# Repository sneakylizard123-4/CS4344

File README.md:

# CS4344 I2S DAC Breakout

**A compact 24-bit / 192 kHz stereo DAC for I2S audio projects.**

`SPDX-License-Identifier: CERN-OHL-P-2.0`

## Overview

The CS4344 is a 24-bit stereo DAC that accepts I2S audio and runs from a single 3.3 V supply. This board gives it a 6-pin 2.54 mm header, a 3.5 mm stereo jack, and the passives it needs. There is no configuration bus. The DAC is in hardware mode, so the host only has to provide clocks and data.

The PCB is 18.5 x 25.0 mm, two layers. The repository also includes a STEP assembly, a parametric 3D-printable case, and an ESP32-S3 test firmware example.

## Why I made this

I wanted a small, reusable I2S output board for FPGA and microcontroller projects.
The CS4344 is inexpensive, supports 24-bit / 192 kHz audio, and has a simple hardware interface.
The board has a real jack so it can be used outside a breadboard.

## Custom features

- 24-bit, up to 192 kHz stereo DAC.
- Hardware-mode I2S input. No I2C or SPI setup.
- Single 3.3 V supply.
- 6-pin 2.54 mm header for power and I2S.
- 3.5 mm stereo SMD jack.
- AC-coupled outputs with 3.3 uF series capacitors, 470 ohm series resistors, and 10 k bleed resistors.
- Compact 18.5 x 25.0 mm two-layer PCB.
- Two-part 3D-printable enclosure with a jack opening, header slot, and M2 screw posts.
- Full STEP assembly and parametric CadQuery source.

## How it works

The signal path is short: I2S comes in on J2, the CS4344 converts it, and the output network drives the jack.

| Block | Main parts | Function |
|---|---|---|
| I2S input | J2 | 3.3 V, ground, SD, SCK, FS, and MCLK |
| DAC | U1 | CS4344 stereo I2S DAC |
| Analog output | C6, C7, R1-R4, J1 | AC coupling, series resistance, and 3.5 mm output |
| Supply and reference decoupling | C1-C5 | VA, VQ, and FILT+ decoupling |

### Power tree

```text
J2.1  +3.3V ---+--- U1.9  VA
               |
               +--- C3 1 uF --- GND
               |
               +--- C5 100 nF --- GND

U1.5  VQ ------+--- C1 10 uF --- GND
               |
               +--- C2 100 nF --- GND

U1.6  FILT+ ---+--- C4 10 uF --- GND
```

The CS4344 is a 3.3 V part. Do not power the board from 5 V. VQ and FILT+ are internal reference/filter nodes; they are decoupled on the board and must not be driven from outside.

### I2S input

```text
J2.2  SD   -> U1.1  SDIN
J2.3  SCK  -> U1.2  SCLK
J2.4  FS   -> U1.3  LRCK
J2.5  MCLK -> U1.4  MCLK
```

The host must supply MCLK. There is no oscillator on the board. The CS4344 accepts several MCLK-to-FS ratios in hardware mode; check the datasheet for the ratio your host uses.

### Analog output

```text
U1.7  AOUTL -> C7 3.3 uF -> node L -> R4 470 ohm -> J1 tip
                              |
                              +-> R1 10 k -> GND

U1.10 AOUTR -> C6 3.3 uF -> node R -> R3 470 ohm -> J1 ring
                              |
                              +-> R2 10 k -> GND

J1 sleeve -> GND
```

Each output is AC-coupled so the DAC's DC bias does not appear at the jack. The 10 k resistor keeps the coupling capacitor's output node referenced to ground, and the 470 ohm resistor limits current into the cable. This is a line-level output, not a headphone amplifier. Use an external headphone amp or powered speakers if you need more drive.

## Schematic

The design is split into four KiCad sheets:

- [Root](images/schematic/01-root.png)
- [CS4344 and output network](images/schematic/02-cs4344.png)
- [3.5 mm jack](images/schematic/03-jack.png)
- [I2S header](images/schematic/04-connector.png)

## PCB design

- 18.5 x 25.0 mm board, 1.6 mm FR-4, two copper layers.
- 1 mm rounded corners.
- 0.2 mm signal traces, 0.5 mm output traces, 0.3 mm via drills.
- The board has no mounting holes.

| Top | Bottom |
|---|---|
|  |  |

More views:

- [Top 3D render](images/pcb/render-top.png)
- [Bottom 3D render](images/pcb/render-bottom.png)
- [Isometric 3D render](images/pcb/render-iso.png)

## Enclosure

The case is a two-part print: a base with screw posts and board ledges, and a lid with a header slot, registration lips, and a hold-down rib. The jack opening is on the right-hand wall. The lid is fixed with four M2 self-tapping screws. The outside size is 30 x 36 mm, 19.4 mm tall with the lid fitted and 20.8 mm including the screw heads.

| Assembled | Cutaway | Exploded |
|---|---|---|
|  |  |  |

The enclosure is parametric CadQuery. Edit the constants at the top of `cad/enclosure.py` and rerun the script to regenerate the STEP and STL files. The full board and case assembly is in `cad/CS4344-full-assembly.step`, and the board and electronics assembly is in `cad/CS4344-assembly.step`. It has not been printed or test-fitted yet.

Suggested print settings:

- 0.2 mm layer height
- 4 perimeters
- 20% infill
- PLA or PETG
- M2 x 8 mm self-tapping screws

## Usage

1. Connect 3.3 V to J2 pin 1 and ground to J2 pin 6.
2. Connect the host's I2S data, bit clock, and frame clock to SD, SCK, and FS.
3. Connect a master clock to MCLK. The board does not generate one.
4. Connect a 3.5 mm stereo cable from J1 to your amplifier or powered speakers.
5. Enable the I2S output on the host and start playback.

Use 3.3 V logic levels. The board does not include level shifters.

### Pinout

| J2 pin | Signal | Direction | Notes |
|---|---|---|---|
| 1 | +3.3V | Power in | 3.3 V only |
| 2 | SD | Input | I2S serial data |
| 3 | SCK | Input | I2S bit clock |
| 4 | FS | Input | I2S frame clock / LRCK |
| 5 | MCLK | Input | Master clock, required |
| 6 | GND | Power | Ground |

| J1 contact | Signal |
|---|---|
| Tip | Left channel |
| Ring | Right channel |
| Sleeve | Ground |

There is no firmware on the board. The host does all of the I2S setup. An ESP32-S3 test example is in `firmware/`.

## Firmware

The board has no MCU, so the firmware in `firmware/` runs on a host board. The example targets an ESP32-S3-DevKitC-1 and outputs a 1 kHz stereo sine at 48 kHz. It is meant as a bring-up test for the DAC and the analog output path.

`SPDX-License-Identifier: MIT`

| Signal | CS4344 J2 pin | ESP32-S3 pin |
|---|---|---|
| +3.3 V | 1 | 3V3 |
| SD | 2 | GPIO6 |
| SCK | 3 | GPIO4 |
| FS | 4 | GPIO5 |
| MCLK | 5 | GPIO7 |
| GND | 6 | GND |

The example runs I2S in standard mode with MCLK at 12.288 MHz, BCLK at 3.072 MHz, and LRCK at 48 kHz. It writes 24-bit samples left-aligned in 32-bit slots. The 32-bit slot keeps the 64 x Fs bit clock that the CS4344 expects. See [firmware/README.md](firmware/README.md) for the build, flash, and test steps.

```sh
cd firmware
pio run
pio run -t upload
pio device monitor
```

The example compiles but has not been run on a fabricated board yet.

## BOM

Prices are in USD and cover one set of electronics, the five-board JLCPCB minimum, and a 10-pack of M2 screws. Shipping, tax, and assembly fees are not included. The root [BOM.csv](BOM.csv) has a purchase link on every part line.

| Ref | Qty | Part | Package | Supplier | Part number | Unit price |
|---|---|---|---|---|---|---|
| U1 | 1 | CS4344-CZZR | TSSOP-10 | LCSC | C8952 | $1.5154 |
| J1 | 1 | SJ-3523-SMT-TR | SMD jack | Digi-Key | CP-3523SJCT-ND | $0.8800 |
| J2 | 1 | 1x6 2.54 mm female header | THT | LCSC | C40877 | $0.0889 |
| C1, C4 | 2 | 10 uF 10 V X5R | 0603 | LCSC | C19702 | $0.0272 |
| C2, C5 | 2 | 100 nF 50 V X7R | 0603 | LCSC | C14663 | $0.0084 |
| C3 | 1 | 1 uF 50 V X5R | 0603 | LCSC | C15849 | $0.0146 |
| C6, C7 | 2 | 3.3 uF 10 V X5R | 0603 | LCSC | C51412 | $0.0601 |
| R1, R2 | 2 | 10 k 1% | 0603 | LCSC | C25804 | $0.0022 |
| R3, R4 | 2 | 470 ohm 1% | 0603 | LCSC | C23179 | $0.0023 |
| PCB | 5 | CS4344 PCB | 18.5 x 25 mm | JLCPCB | - | $0.4000 |
| HW1 | 1 | M2 x 8 mm self-tapping screw, 10-pack | M2 | Motion RC | BCT5040-022 | $1.0900 |

| | |
|---|---:|
| Electronics subtotal | $2.6993 |
| 5 PCBs | $2.0000 |
| Screws, 10-pack | $1.0900 |
| **Total, excluding shipping and tax** | **$5.7893** |

That total buys one set of electronics, five bare PCBs, and a 10-pack of screws. You can build one board, keep four spare PCBs, and use 4 of the 10 screws.

The exact CUI jack is out of stock at LCSC. The Digi-Key part is the same SJ-3523-SMT-TR and was in stock when I checked.

## Production

Fabrication files are in `kicad/production/`:

- `CS4344.zip` - Gerbers and drill files.
- `bom.csv` - assembly BOM.
- `positions.csv` - pick-and-place positions.
- `designators.csv` - designator list.
- `netlist.ipc` - IPC netlist.

The board has not been ordered yet. The enclosure has not been printed yet.

## Repository structure

```text
CS4344/
|-- README.md
|-- JOURNAL.md
|-- BOM.csv
|-- LICENSE
|-- LICENSE-MIT
|-- .gitignore
|-- kicad/
|   |-- CS4344.kicad_pro
|   |-- CS4344.kicad_sch
|   |-- connector.kicad_sch
|   |-- cs4344.kicad_sch
|   |-- jack.kicad_sch
|   |-- CS4344.kicad_pcb
|   |-- sym-lib-table
|   |-- fabrication-toolkit-options.json
|   `-- production/
|       |-- CS4344.zip
|       |-- bom.csv
|       |-- designators.csv
|       |-- netlist.ipc
|       `-- positions.csv
|-- cad/
|   |-- enclosure.py
|   |-- CS4344-assembly.step
|   |-- CS4344-board.step
|   |-- CS4344-enclosure-base.step
|   |-- CS4344-enclosure-base.stl
|   |-- CS4344-enclosure-lid.step
|   |-- CS4344-enclosure-lid.stl
|   `-- CS4344-full-assembly.step
|-- firmware/
|   |-- README.md
|   |-- platformio.ini
|   `-- src/
|       `-- main.cpp
|-- images/
|   |-- schematic/       (screenshots as .png)
|   |-- pcb/             (editor screenshot)
|   |-- assembly/        (exploded)
|   `-- screenshots/     (timestamped progress images)
`-- blender/
    |-- CS4344.blend
    `-- CS4344.pcb3d
```

## Known issues

- The board has not been fabricated or tested. This is a first revision.
- The enclosure has not been printed or test-fitted.
- The lid counterbores are 4.2 mm across. Check the head diameter of the screws you buy and enlarge the counterbores if needed.
- The screws in the STEP assembly are simplified cylinders, not the exact screw geometry.
- The board has no mounting holes. It is held by the case ledges and lid rib.
- The CS4344 is TSSOP-10 with 0.5 mm pin pitch. It is not a good first hand-soldering project; use a stencil and hot air or reflow.
- The output is line level. It will not drive headphones directly.
- The ESP32-S3 firmware example compiles but has not been run on a fabricated board.

## Credits and inspiration

- Cirrus Logic for the CS4344 datasheet and reference circuit.
- KiCad for the schematic and PCB tools.
- CadQuery for the parametric enclosure.
- Hack Club Forge for the deadline and the push to document the project.

## License

Hardware design files and documentation are licensed under the CERN Open Hardware Licence Version 2 - Permissive (CERN-OHL-P-2.0). See [LICENSE](LICENSE).

`SPDX-License-Identifier: CERN-OHL-P-2.0`

The example firmware in `firmware/` is licensed under the MIT License. See [LICENSE-MIT](LICENSE-MIT).

`SPDX-License-Identifier: MIT`

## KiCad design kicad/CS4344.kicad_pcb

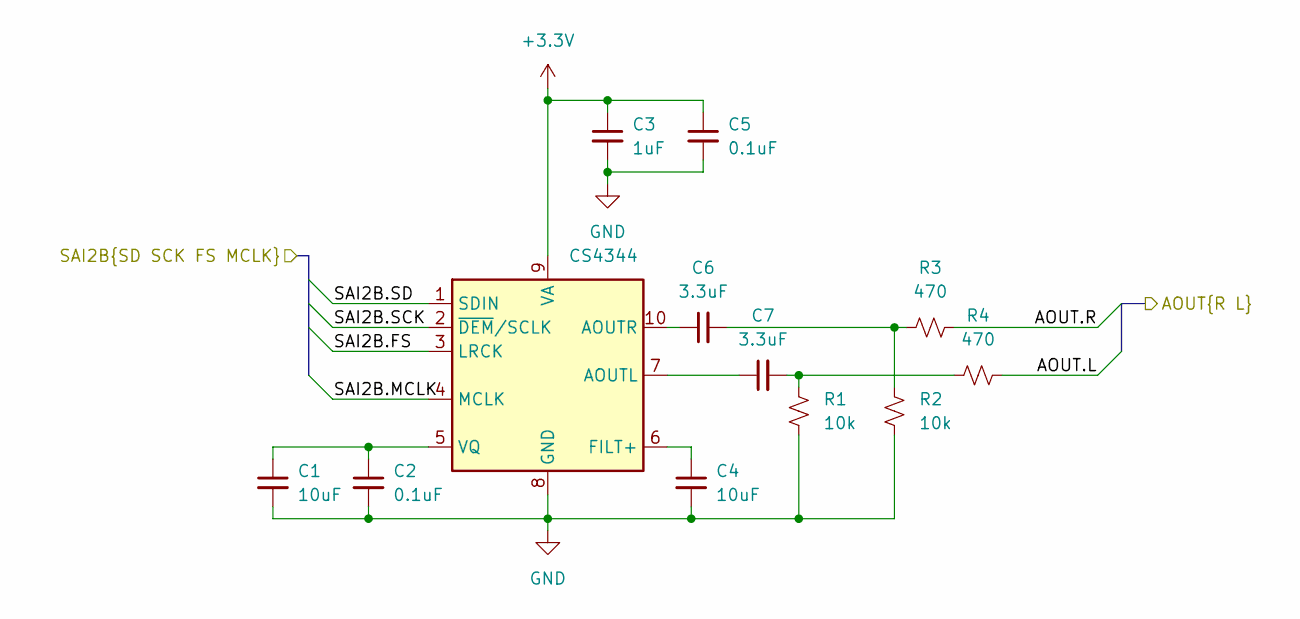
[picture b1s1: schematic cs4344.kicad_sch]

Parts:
C1, C4: 10uF; C_0603_1608Metric
C2, C5: 0.1uF; C_0603_1608Metric
C3: 1uF; C_0603_1608Metric
C6, C7: 3.3uF; C_0603_1608Metric
R1, R2: 10k; R_0603_1608Metric
R3, R4: 470; R_0603_1608Metric
U1: CS4344; TSSOP-10_3x3mm_P0.5mm

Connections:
+3.3V: C3.1, C5.1, U1.9 (VA); also elsewhere on the board
/CS4344/AOUT.L: R4.2; also elsewhere on the board
/CS4344/AOUT.R: R3.2; also elsewhere on the board
/CS4344/SAI2B.FS: U1.3 (LRCK); also elsewhere on the board
/CS4344/SAI2B.MCLK: U1.4 (MCLK); also elsewhere on the board
/CS4344/SAI2B.SCK: U1.2 (~DEM/SCLK); also elsewhere on the board
/CS4344/SAI2B.SD: U1.1 (SDIN); also elsewhere on the board
GND: C1.2, C2.2, C3.2, C4.2, C5.2, R1.2, R2.2, U1.8 (GND); also elsewhere on the board
unnamed: C6.2, R2.1, R3.1
unnamed: C7.2, R1.1, R4.1
unnamed: C7.1, U1.7 (AOUTL)
unnamed: C6.1, U1.10 (AOUTR)
unnamed: C4.1, U1.6 (FILT+)
unnamed: C1.1, C2.1, U1.5 (VQ)

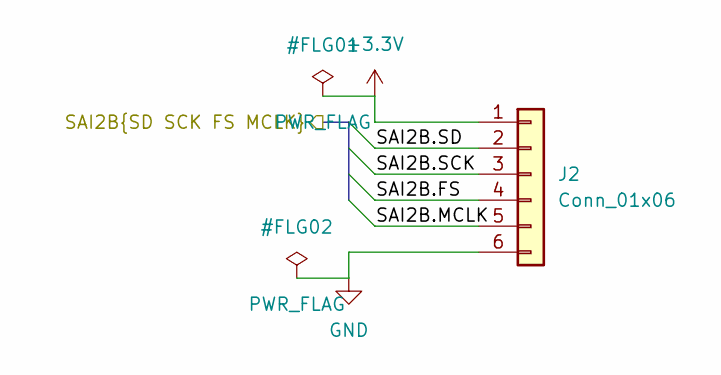
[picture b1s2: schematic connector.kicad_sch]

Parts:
J2: Conn_01x06; PinSocket_1x06_P2.54mm_Vertical

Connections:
+3.3V: J2.1; also elsewhere on the board
/CS4344/SAI2B.FS: J2.4; also elsewhere on the board
/CS4344/SAI2B.MCLK: J2.5; also elsewhere on the board
/CS4344/SAI2B.SCK: J2.3; also elsewhere on the board
/CS4344/SAI2B.SD: J2.2; also elsewhere on the board
GND: J2.6; also elsewhere on the board

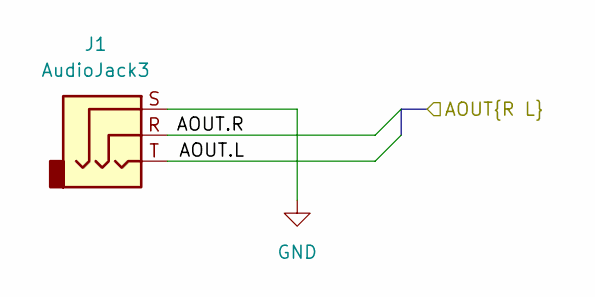
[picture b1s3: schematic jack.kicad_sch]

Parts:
J1: AudioJack3; Jack_3.5mm_CUI_SJ-3523-SMT_Horizontal

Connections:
/CS4344/AOUT.L: J1.T; also elsewhere on the board
/CS4344/AOUT.R: J1.R; also elsewhere on the board
GND: J1.S; also elsewhere on the board

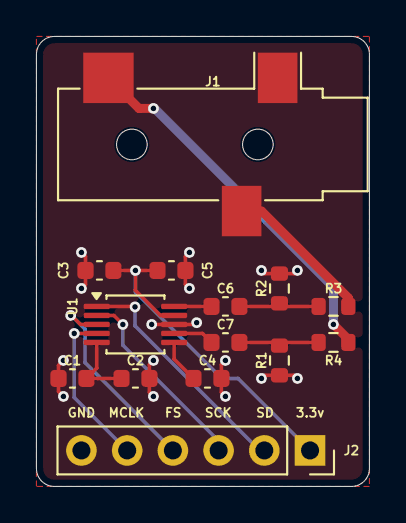
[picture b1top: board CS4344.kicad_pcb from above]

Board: 2 copper layers, 18.5 x 25.0 mm, 14 parts (0 on the bottom side), 14 nets.

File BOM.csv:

Item,Qty,Reference,Value,Description,Package,Supplier,Part Number,Unit Price (USD),Line Total (USD),Link
1,1,U1,CS4344,24-bit 192 kHz stereo I2S DAC,TSSOP-10,LCSC,C8952,1.5154,1.5154,https://www.lcsc.com/product-detail/C8952.html
2,1,J1,SJ-3523-SMT-TR,3.5 mm stereo audio jack SMD,SMD,Digi-Key,CP-3523SJCT-ND,0.8800,0.8800,https://www.digikey.com/en/products/detail/same-sky-formerly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
3,1,J2,1x6 2.54 mm female header,6-pin 2.54 mm through-hole socket,THT,LCSC,C40877,0.0889,0.0889,https://www.lcsc.com/product-detail/C40877.html
4,1,C1,10 uF,10 uF 10 V X5R 0603 capacitor,0603,LCSC,C19702,0.0272,0.0272,https://www.lcsc.com/product-detail/C19702.html
5,1,C2,100 nF,100 nF 50 V X7R 0603 capacitor,0603,LCSC,C14663,0.0084,0.0084,https://www.lcsc.com/product-detail/C14663.html
6,1,C3,1 uF,1 uF 50 V X5R 0603 capacitor,0603,LCSC,C15849,0.0146,0.0146,https://www.lcsc.com/product-detail/C15849.html
7,1,C4,10 uF,10 uF 10 V X5R 0603 capacitor,0603,LCSC,C19702,0.0272,0.0272,https://www.lcsc.com/product-detail/C19702.html
8,1,C5,100 nF,100 nF 50 V X7R 0603 capacitor,0603,LCSC,C14663,0.0084,0.0084,https://www.lcsc.com/product-detail/C14663.html
9,1,C6,3.3 uF,3.3 uF 10 V X5R 0603 capacitor,0603,LCSC,C51412,0.0601,0.0601,https://www.lcsc.com/product-detail/C51412.html
10,1,C7,3.3 uF,3.3 uF 10 V X5R 0603 capacitor,0603,LCSC,C51412,0.0601,0.0601,https://www.lcsc.com/product-detail/C51412.html
11,1,R1,10 k,10 k 1% 0603 resistor,0603,LCSC,C25804,0.0022,0.0022,https://www.lcsc.com/product-detail/C25804.html
12,1,R2,10 k,10 k 1% 0603 resistor,0603,LCSC,C25804,0.0022,0.0022,https://www.lcsc.com/product-detail/C25804.html
13,1,R3,470,470 ohm 1% 0603 resistor,0603,LCSC,C23179,0.0023,0.0023,https://www.lcsc.com/product-detail/C23179.html
14,1,R4,470,470 ohm 1% 0603 resistor,0603,LCSC,C23179,0.0023,0.0023,https://www.lcsc.com/product-detail/C23179.html
15,5,PCB,CS4344 PCB,2-layer 1.6 mm FR-4 PCB 18.5 x 25 mm (minimum order 5),-,JLCPCB,CS4344,0.4000,2.0000,https://jlcpcb.com/
16,1,HW1,M2 x 8 mm screw,"M2 x 8 mm self-tapping screw, 10-pack (4 used)",M2,Motion RC,BCT5040-022,1.0900,1.0900,https://motionrc.com/products/benchcraft-2mm-x-8mm-self-tapp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
,,,,SUBTOTAL (electronics),,,,,2.6993,
,,,,"TOTAL (electronics + 5 PCBs + screws, excl. shipping and tax)",,,,,5.7893,
